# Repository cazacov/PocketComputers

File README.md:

# Pocket Computers
My experiments with programmable calculators and pocket computers.

## Sharp Pocket Computer PC-E500 / PC-E500s

### RAM upgrade to 128K

[PC-E500/E500s RAM upgrade project](./sharp-e500/RAM-upgrade)

### DIY 256K RAM card

[DIY 256K RAM card project](./sharp-e500/RAM-card)

---
All trademarks, logos and brand names are the property of their respective owners. All company, product and service names are for identification purposes only. 

I am not an electronics engineer. It's a hobby project. Use it at your own risk.

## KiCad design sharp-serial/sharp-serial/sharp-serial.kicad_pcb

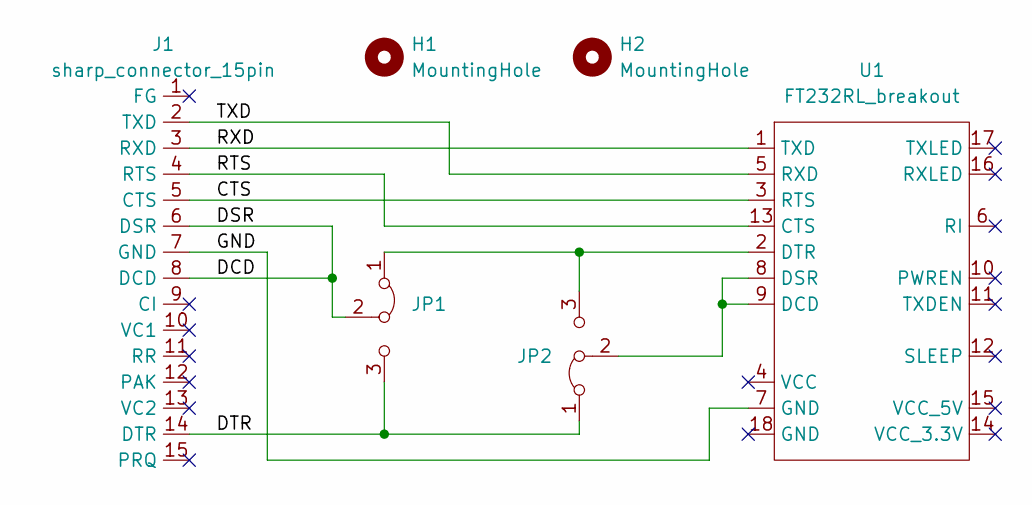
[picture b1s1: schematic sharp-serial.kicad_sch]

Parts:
H1, H2: MountingHole; MountingHole_2.5mm
J1: sharp_connector_15pin
JP1, JP2: Jumper_3_Bridged12; PinHeader_1x03_P2.54mm_Vertical
U1: FT232RL_breakout

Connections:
unnamed: J1.2 (TXD), U1.5 (RXD)
unnamed: J1.3 (RXD), U1.1 (TXD)
unnamed: J1.4 (RTS), U1.13 (CTS)
unnamed: J1.5 (CTS), U1.3 (RTS)
unnamed: J1.6 (DSR), J1.8 (DCD), JP1.2 (C)
unnamed: J1.7 (GND), U1.7 (GND)
unnamed: J1.14 (DTR), JP1.3 (B), JP2.1 (A)
unnamed: JP1.1 (A), JP2.3 (B), U1.2 (DTR)
unnamed: JP2.2 (C), U1.8 (DSR), U1.9 (DCD)

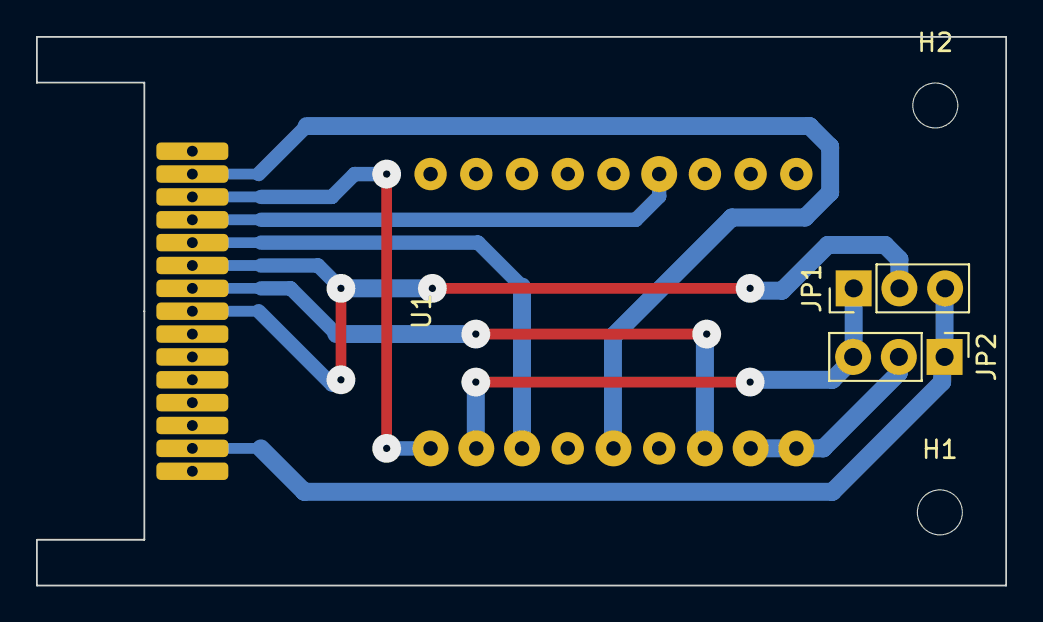
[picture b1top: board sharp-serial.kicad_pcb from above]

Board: 2 copper layers, 53.8 x 30.5 mm, 6 parts (1 on the bottom side), 9 nets.

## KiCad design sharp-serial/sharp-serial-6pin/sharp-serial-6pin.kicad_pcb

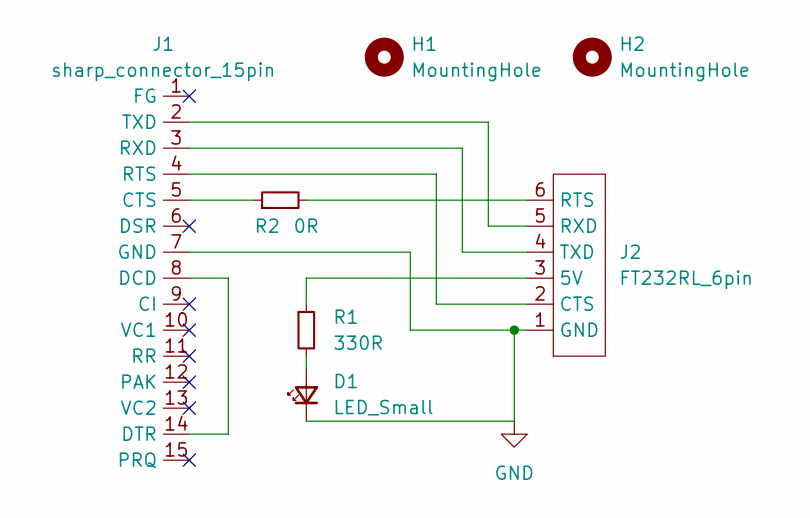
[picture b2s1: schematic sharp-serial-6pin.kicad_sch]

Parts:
D1: LED_Small; LED_D3.0mm
H1, H2: MountingHole; MountingHole_3.2mm_M3
J1: sharp_connector_15pin
J2: FT232RL_6pin; FT232RL_6pins
R1: 330R; R_1206_3216Metric
R2: 0R; R_1206_3216Metric

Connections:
GND: D1.1 (K), J1.7 (GND), J2.1 (GND)
unnamed: J1.2 (TXD), J2.5 (RXD)
unnamed: J1.3 (RXD), J2.4 (TXD)
unnamed: J1.4 (RTS), J2.2 (CTS)
unnamed: J1.5 (CTS), R2.1
unnamed: J1.8 (DCD), J1.14 (DTR)
unnamed: J2.3 (5V), R1.1
unnamed: D1.2 (A), R1.2
unnamed: J2.6 (RTS), R2.2

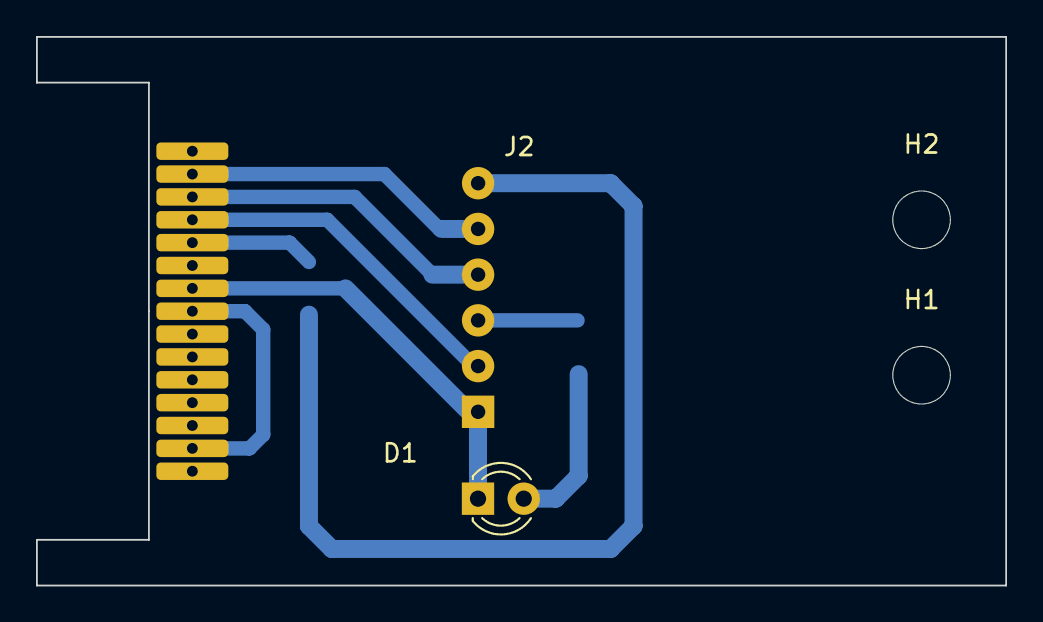
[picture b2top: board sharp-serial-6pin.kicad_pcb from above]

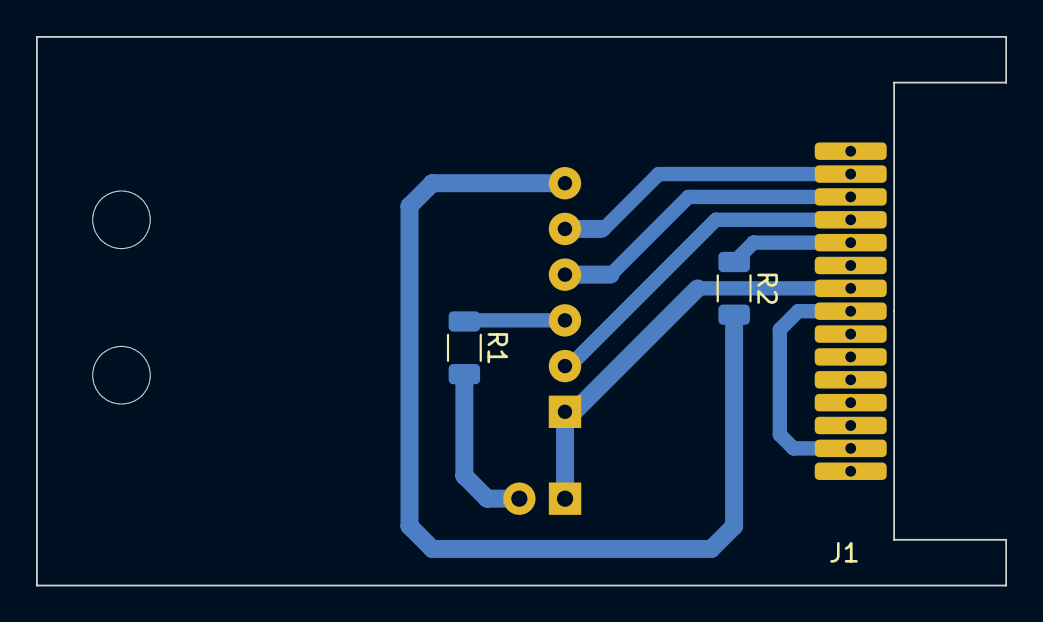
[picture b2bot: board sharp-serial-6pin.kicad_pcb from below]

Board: 2 copper layers, 53.8 x 30.5 mm, 7 parts (3 on the bottom side), 9 nets.

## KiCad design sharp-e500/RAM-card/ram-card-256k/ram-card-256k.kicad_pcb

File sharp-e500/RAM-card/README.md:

# RAM Card for Sharp Pocket PC-E500

Disclaimer: use it at your own risk. I am programmer, not an electronics engineer. The DIY card works for me but can damage your device.

256 KB RAM card with battery.

## Circuit Diagram

[Download as PDF](./ram-card-256k/ram-card-256k.pdf)

[KiCad Project](./ram-card-256k/)

## PCB

PCB: 41.9 x 54.1 x 0.8 mm

## Bill of Materials

| Reference | Part | Size | Comments |
| --------- | ---- | ---- | -------- |
| R1,R2 | 47K | 1206 | Pull resistor |
| R3 | 470K | 1206 | Pull resistor |
| C1 | 330 nF | 1812 | Decoupling capacitor |
| D1 | RB160M | SOD-123 | Schottky diode prevents card battery trying to power E500 when it's switched off |
| D2 | 1N4148W | SOD-123 | Fast switching diode - reverse battery protection, prevents cell battery loading from E500 |
| U1 | HC138 | SOIC-16 | Address decoder |
| U2, U3 | KM681000BLG | SSOP-32 | 128K x 8-bit low power CMOS static RAM |
| S1 | Slider switch | 6.7 x 2.7 mm | Write protection |
| BT1 | CR1216 | 12.5 x 1.6 mm | 3 volts lithium cell |

## Usage

Power off Pocket Computer, insert card, power on.

The following message should appear:
```
S2(CARD):NEW CARD

   PF1 --- INITIALIZE
   PF2 --- DO NOT INITIALIZE
```

Press **PF1** to initialize.

To use card as an additional memory space for Basic program and variables type:

```
MEM$="B"
```

To use internal RAM for storing programs and variables

```
MEM$="S1"
```

To use RAM card for storing programs and variables

```
MEM$="S2"
```

### Device names

- **X:** Pocket disk drive
- **Y:** Another disk in the disk drive. Used for disk-to-disk copy
- **E:** RAM disk internal RAM
- **F:** RAM disk external RAM
- **G:** ROM storing engineering programs
- **CAS:** Cassette tape
- **COM:** Serial I/O device

### Partitioning RAM card

The card space is used for storing data and variables.

Allocate **data** storage space in the RAM disk F: 

```
INIT "F:100K"
```

*Allowable size can be from 2 to RAM card capacity minus 1.*

### Usage example

```BASIC
REM use internal RAM for BASIC programs and variables
MEM$="S1"

REM reserve 254K for data on external RAM drive F:
INIT "F:254K"     

REM check free variables space (internal RAM)
FRE 0

REM check free disk space on external RAM card
DSKF "F:"

REM check what files are delivered with E500 on built-in ROM
FILES "G:"

REM copy pre-installed program with periodic table of chemical elements from ROM to F:
COPY "G:PERIOD.221" TO "F:"

REM check that file is now present on drive F:
FILES "F:"

REM check the remaining free disk space (must be ~8K less than on a newly initialized card)
DSKF "F:"

REM test if information is preserved on the RAM card when not inserted in E500 (CR1216 cell should provide enough power to store data for few months)

REM turn off Pocket Computer
REM take out the RAM card
REM turn on Pocket computer
FILES "F:"
--> Bad drive name

REM turn off Pocket Computer
REM put the RAM card back into E500
REM turn on Pocket computer
FILES "F:"
--> you should see list of files

REM load file from F:
LOAD "F:PERIOD.221"

REM switch to PROG mode clicking green BASIC button
REM check that file was loaded
LIST

REM switch back to RUN mode clicking BASIC button again
REM execute the program
RUN
```

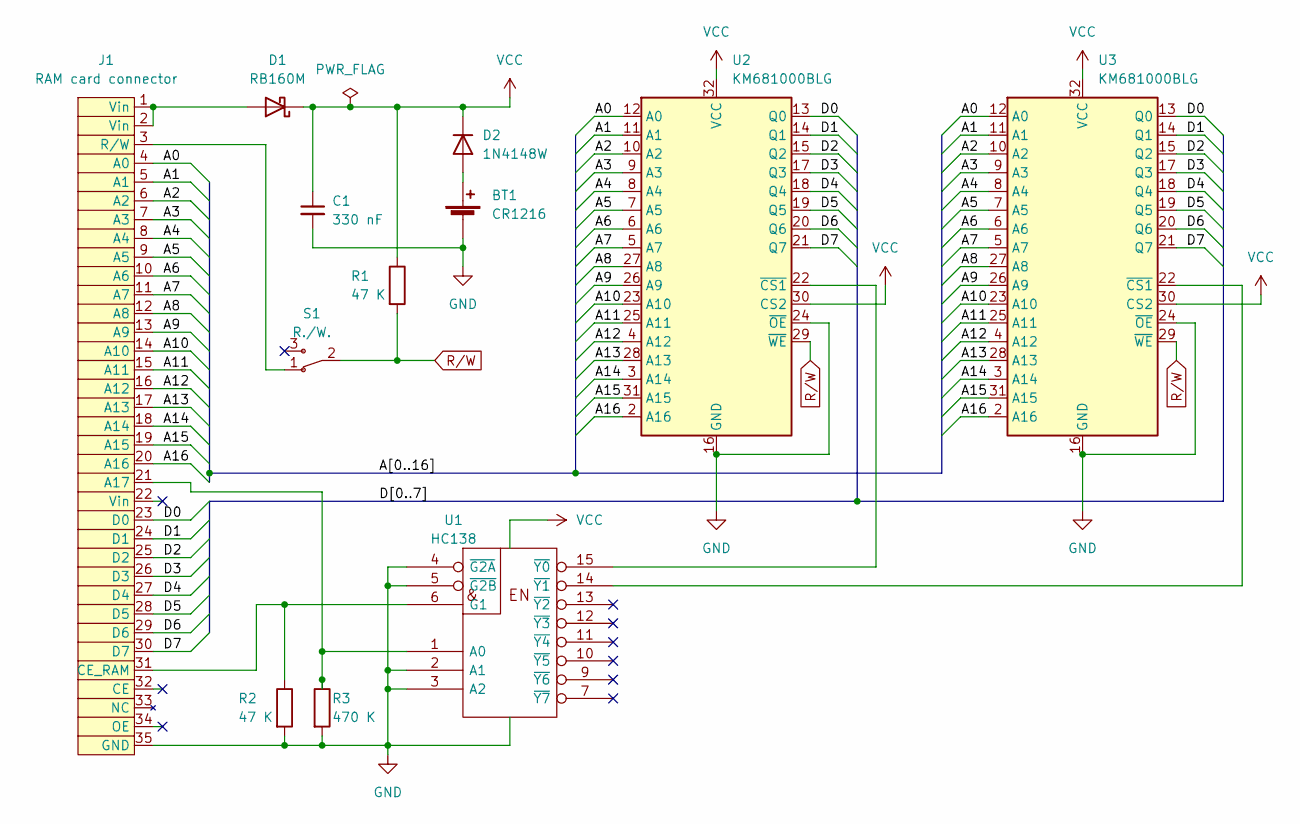
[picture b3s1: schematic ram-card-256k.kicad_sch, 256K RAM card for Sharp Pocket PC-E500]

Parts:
BT1: CR1216; Battery_CR1216_hole
C1: 330 nF; C_1812_4532Metric
D1: RB160M; D_SOD-123
D2: 1N4148W; D_SOD-123
J1: RAM card connector; RAM_card_connector_35
R1, R2: 47 K; R_1206_3216Metric
R3: 470 K; R_1206_3216Metric
S1: R./W.; slider_switch_7x3
U1: HC138; SOIC-16_3.9x9.9mm_P1.27mm
U2, U3: KM681000BLG; SSOP-32_11.305x20.495mm_P1.27mm

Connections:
/A0: J1.4 (A0), U2.12 (A0), U3.12 (A0)
/A1: J1.5 (A1), U2.11 (A1), U3.11 (A1)
/A2: J1.6 (A2), U2.10 (A2), U3.10 (A2)
/A3: J1.7 (A3), U2.9 (A3), U3.9 (A3)
/A4: J1.8 (A4), U2.8 (A4), U3.8 (A4)
/A5: J1.9 (A5), U2.7 (A5), U3.7 (A5)
/A6: J1.10 (A6), U2.6 (A6), U3.6 (A6)
/A7: J1.11 (A7), U2.5 (A7), U3.5 (A7)
/A8: J1.12 (A8), U2.27 (A8), U3.27 (A8)
/A9: J1.13 (A9), U2.26 (A9), U3.26 (A9)
/A10: J1.14 (A10), U2.23 (A10), U3.23 (A10)
/A11: J1.15 (A11), U2.25 (A11), U3.25 (A11)
/A12: J1.16 (A12), U2.4 (A12), U3.4 (A12)
/A13: J1.17 (A13), U2.28 (A13), U3.28 (A13)
/A14: J1.18 (A14), U2.3 (A14), U3.3 (A14)
/A15: J1.19 (A15), U2.31 (A15), U3.31 (A15)
/A16: J1.20 (A16), U2.2 (A16), U3.2 (A16)
/D0: J1.23 (D0), U2.13 (Q0), U3.13 (Q0)
/D1: J1.24 (D1), U2.14 (Q1), U3.14 (Q1)
/D2: J1.25 (D2), U2.15 (Q2), U3.15 (Q2)
/D3: J1.26 (D3), U2.17 (Q3), U3.17 (Q3)
/D4: J1.27 (D4), U2.18 (Q4), U3.18 (Q4)
/D5: J1.28 (D5), U2.19 (Q5), U3.19 (Q5)
/D6: J1.29 (D6), U2.20 (Q6), U3.20 (Q6)
/D7: J1.30 (D7), U2.21 (Q7), U3.21 (Q7)
GND: BT1.2 (-), C1.2, J1.35 (GND), R2.2, R3.2, U1.2 (A1), U1.3 (A2), U1.4 (~G2A), U1.5 (~G2B), U1.8 (GND), U2.16 (GND), U2.24 (~OE), U3.16 (GND), U3.24 (~OE)
unnamed: BT1.1 (+), D2.2 (A)
unnamed: D1.2 (A), J1.1 (Vin), J1.2 (Vin)
unnamed: J1.3 (R/W), S1.1
unnamed: J1.21 (A17), R3.1, U1.1 (A0)
unnamed: J1.31 (CE_RAM), R2.1, U1.6 (G1)
unnamed: U1.14 (~Y1), U3.22 (~CS1)
unnamed: U1.15 (~Y0), U2.22 (~CS1)
R/W: R1.2, S1.2, U2.29 (~WE), U3.29 (~WE)
VCC: C1.1, D1.1 (K), D2.1 (K), R1.1, U1.16 (VCC), U2.30 (CS2), U2.32 (VCC), U3.30 (CS2), U3.32 (VCC)

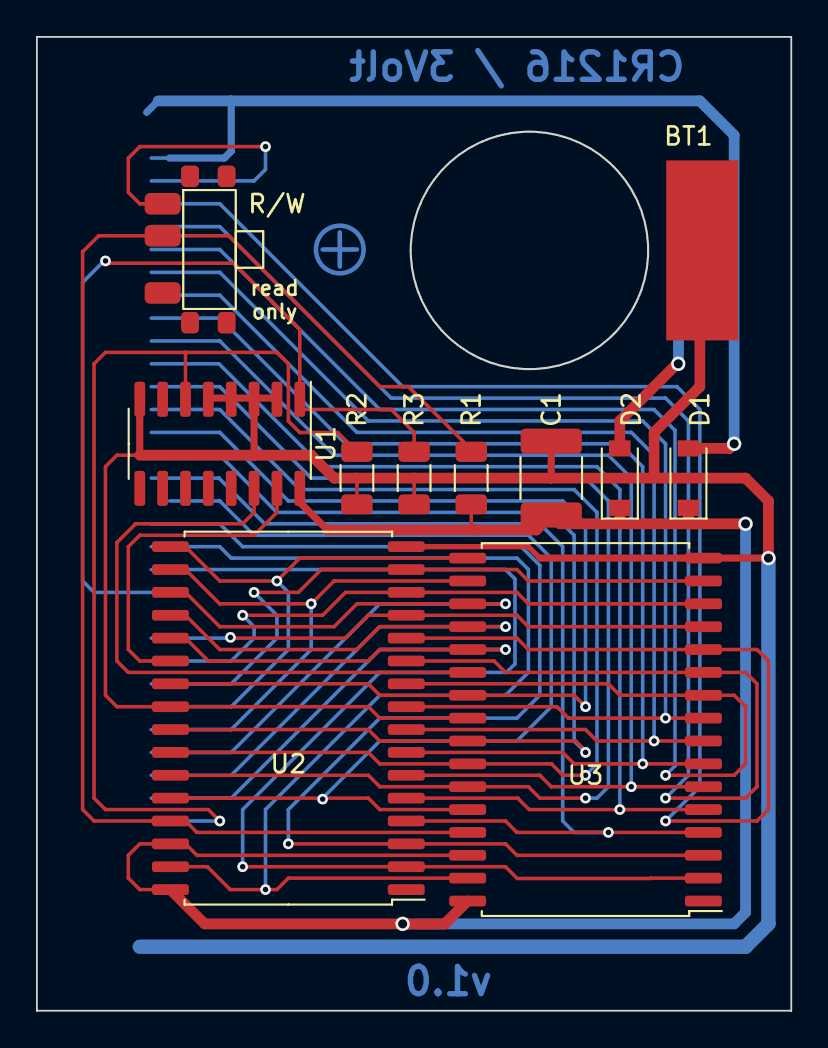
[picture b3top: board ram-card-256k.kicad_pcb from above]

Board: 2 copper layers, 41.9 x 54.1 mm, 12 parts (1 on the bottom side), 35 nets.

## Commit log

2022-10-02 Document Sharp PC-E500 internal RAM upgrade
2022-10-03 Design RAM card for e500
2022-10-04 Design symbol for RAM card connector
2022-10-05 Add custom footprints
2022-10-05 Fix rules check errors
2022-10-06 Improve footprints
2022-10-06 Component layout
2022-10-07 Layout
2022-10-07 ^Layout
2022-10-07 Layout Data bus
2022-10-07 Data bus
2022-10-07 No errors, no warnings
2022-10-08 Version 1.0
2022-10-08 PROD release 1.0
2022-10-09 Assign 3d-model
2022-10-15 Serial cable with full duplex
2022-10-17 Add README
2022-10-17 Documentation
2022-10-21 Document RAM card
2022-10-31 Add 3d-models of support pads
2023-01-23 Add ROM connector for Casio PB-2000
2023-01-23 USB->serial connector for Sharp using 6pins FT232RL cable
2023-01-23 Design ROM card for Casio PB-2000
2023-01-23 Design footprint
